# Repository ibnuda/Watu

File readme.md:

# Watu

Watu (stone in [javanese language](https://en.wikipedia.org/wiki/Javanese_language))
is a split keyboard that is intended for [short hand typing](https://en.wikipedia.org/wiki/Stenotype)
with plover, i guess.

## Pics

Currently in prod.
but see this:

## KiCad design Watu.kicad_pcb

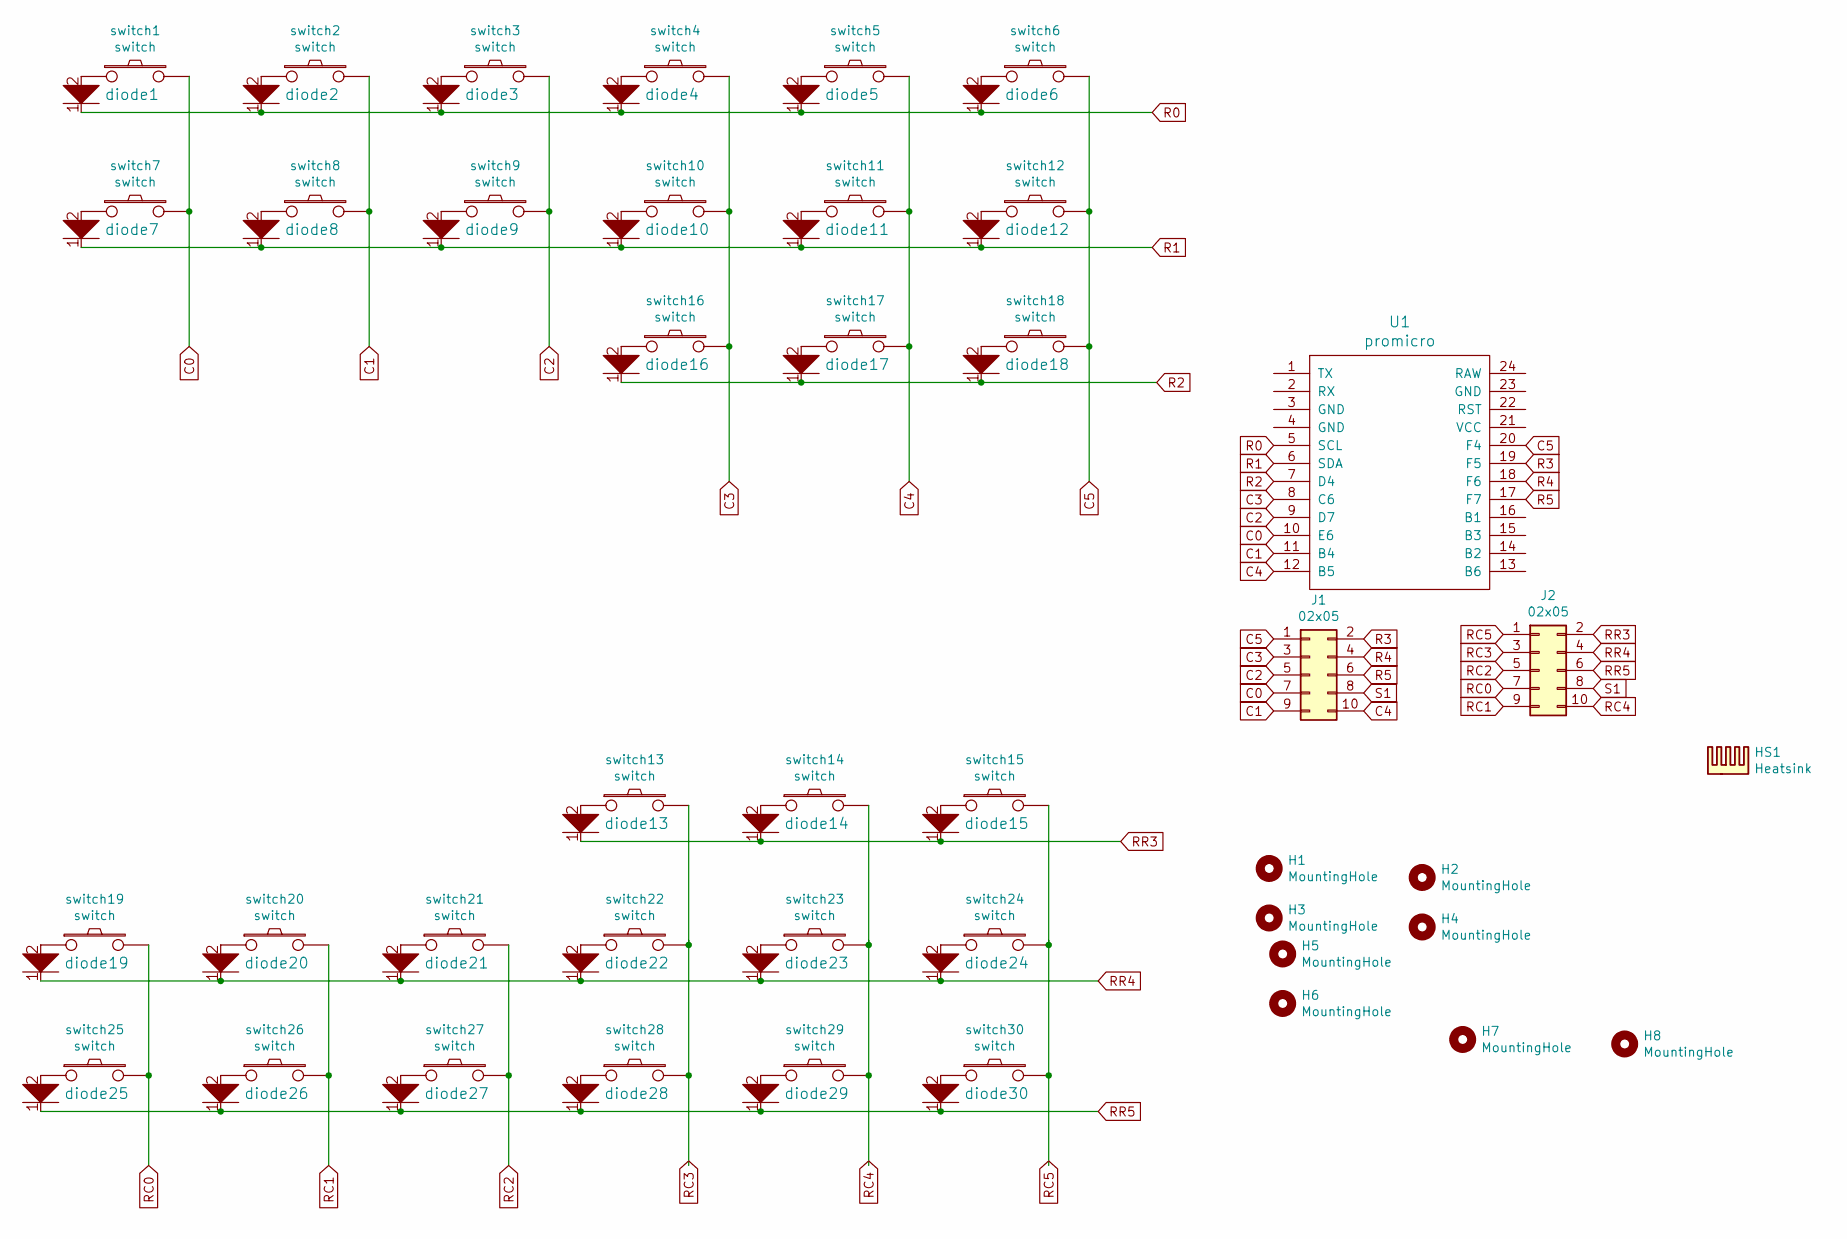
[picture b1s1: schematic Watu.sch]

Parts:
H1, H2, H3, H4, H5, H6: MountingHole; hole-three-bigger
H7, H8: MountingHole; 1-4-mounting-hole
HS1: Heatsink; watu
J1, J2: 02x05; connector-shrouded
U1: promicro
diode1, diode2, diode3, diode4, diode5, diode6, diode7, diode8, diode9, diode10, diode11, diode12, diode13, diode14, diode15, diode16, diode17, diode18, diode19, diode20, diode21, diode22, diode23, diode24, diode25, diode26, diode27, diode28, diode29, diode30: diode
switch1, switch2, switch3, switch4, switch5, switch6, switch7, switch8, switch9, switch10, switch11, switch12, switch13, switch14, switch15, switch16, switch17, switch18, switch19, switch20, switch21, switch22, switch23, switch24, switch25, switch26, switch27, switch28, switch29, switch30: switch; 100-minimal

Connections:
C0: J1.7, U1.10 (E6), switch1.2, switch7.2
C1: J1.9, U1.11 (B4), switch2.2, switch8.2
C2: J1.5, U1.9 (D7), switch3.2, switch9.2
C3: J1.3, U1.8 (C6), switch4.2, switch10.2, switch16.2
C4: J1.10, U1.12 (B5), switch5.2, switch11.2, switch17.2
C5: J1.1, U1.20 (F4), switch6.2, switch12.2, switch18.2
unnamed: diode1.2, switch1.1
unnamed: diode2.2, switch2.1
unnamed: diode3.2, switch3.1
unnamed: diode4.2, switch4.1
unnamed: diode5.2, switch5.1
unnamed: diode6.2, switch6.1
unnamed: diode7.2, switch7.1
unnamed: diode8.2, switch8.1
unnamed: diode9.2, switch9.1
unnamed: diode10.2, switch10.1
unnamed: diode11.2, switch11.1
unnamed: diode12.2, switch12.1
unnamed: diode13.2, switch13.1
unnamed: diode14.2, switch14.1
unnamed: diode15.2, switch15.1
unnamed: diode16.2, switch16.1
unnamed: diode17.2, switch17.1
unnamed: diode18.2, switch18.1
unnamed: diode19.2, switch19.1
unnamed: diode20.2, switch20.1
unnamed: diode21.2, switch21.1
unnamed: diode22.2, switch22.1
unnamed: diode23.2, switch23.1
unnamed: diode24.2, switch24.1
unnamed: diode25.2, switch25.1
unnamed: diode26.2, switch26.1
unnamed: diode27.2, switch27.1
unnamed: diode28.2, switch28.1
unnamed: diode29.2, switch29.1
unnamed: diode30.2, switch30.1
R0: U1.5 (SCL), diode1.1, diode2.1, diode3.1, diode4.1, diode5.1, diode6.1
R1: U1.6 (SDA), diode7.1, diode8.1, diode9.1, diode10.1, diode11.1, diode12.1
R2: U1.7 (D4), diode16.1, diode17.1, diode18.1
R3: J1.2, U1.19 (F5)
R4: J1.4, U1.18 (F6)
R5: J1.6, U1.17 (F7)
RC0: J2.7, switch19.2, switch25.2
RC1: J2.9, switch20.2, switch26.2
RC2: J2.5, switch21.2, switch27.2
RC3: J2.3, switch13.2, switch22.2, switch28.2
RC4: J2.10, switch14.2, switch23.2, switch29.2
RC5: J2.1, switch15.2, switch24.2, switch30.2
RR3: J2.2, diode13.1, diode14.1, diode15.1
RR4: J2.4, diode19.1, diode20.1, diode21.1, diode22.1, diode23.1, diode24.1
RR5: J2.6, diode25.1, diode26.1, diode27.1, diode28.1, diode29.1, diode30.1
S1: J1.8, J2.8

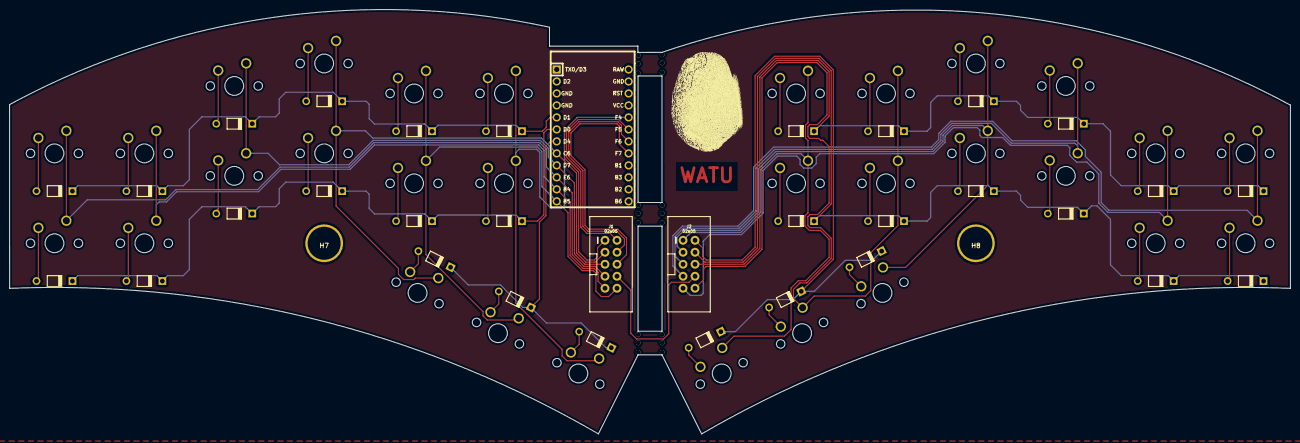
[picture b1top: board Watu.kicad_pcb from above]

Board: 2 copper layers, 271.4 x 89.9 mm, 72 parts (0 on the bottom side), 52 nets.

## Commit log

2021-11-11 init commit.
2021-11-11 readme.
